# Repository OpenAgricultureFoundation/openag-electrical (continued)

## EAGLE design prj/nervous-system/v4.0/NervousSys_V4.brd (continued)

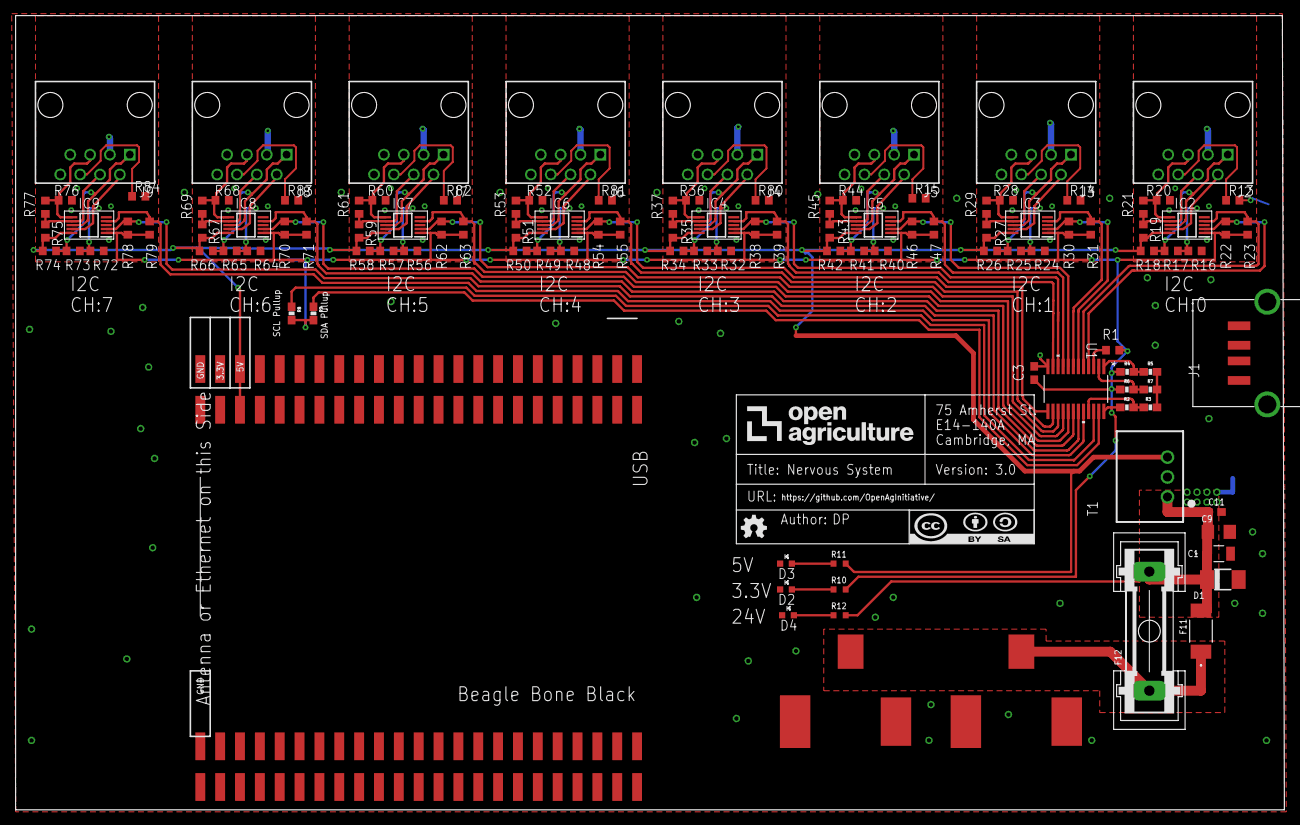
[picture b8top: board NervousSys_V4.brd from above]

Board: 2 copper layers, 162.3 x 101.6 mm, 117 parts (0 on the bottom side), 70 nets.

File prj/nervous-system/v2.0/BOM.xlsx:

Part | Value | Device | Package | Description | Column1 | Column2 | Column3 | Column4 | Column5 | Column6 | Column7 | Column8 | Column9 | Column10 | Column11 | Column12 | Column13 | Column14 | Column15 | Column16 | Column17 | Column18 | Column19 | Column20 | Column21 | Column22 | Column23 | Column24 | Column25
F12 |  | GSH15 | GSH15 | Fuse Holder
C3 | .1uF | C-USC0603 | C0603@1 | 50V or greater
C11 | .1uF | C-USC0603 | C0603@1 | 50V or greater
R1 | 10K | R-US_R0603 | R0603 | 5% tolerance or greater, 1/10W, 0603
R2 | 10K | R-US_R0603 | 0603-RES | 5% tolerance or greater, 1/10W, 0603
R4 | 10K | R-US_R0603 | 0603-RES | 5% tolerance or greater, 1/10W, 0603
R6 | 10K | R-US_R0603 | 0603-RES | 5% tolerance or greater, 1/10W, 0603
R8 | 10K | R-US_R0603 | 0603-RES | 5% tolerance or greater, 1/10W, 0603
R9 | 10K | R-US_R0603 | 0603-RES | 5% tolerance or greater, 1/10W, 0603
R22 | 10K | R-US_R0603 | R0603 | 5% tolerance or greater, 1/10W, 0603
R23 | 10K | R-US_R0603 | R0603 | 5% tolerance or greater, 1/10W, 0604
R30 | 10K | R-US_R0603 | R0603 | 5% tolerance or greater, 1/10W, 0605
R31 | 10K | R-US_R0603 | R0603 | 5% tolerance or greater, 1/10W, 0606
R38 | 10K | R-US_R0603 | R0603 | 5% tolerance or greater, 1/10W, 0607
R39 | 10K | R-US_R0603 | R0603 | 5% tolerance or greater, 1/10W, 0608
R46 | 10K | R-US_R0603 | R0603 | 5% tolerance or greater, 1/10W, 0609
R47 | 10K | R-US_R0603 | R0603 | 5% tolerance or greater, 1/10W, 0610
R54 | 10K | R-US_R0603 | R0603 | 5% tolerance or greater, 1/10W, 0611
R55 | 10K | R-US_R0603 | R0603 | 5% tolerance or greater, 1/10W, 0612
R62 | 10K | R-US_R0603 | R0603 | 5% tolerance or greater, 1/10W, 0613
R63 | 10K | R-US_R0603 | R0603 | 5% tolerance or greater, 1/10W, 0614
R70 | 10K | R-US_R0603 | R0603 | 5% tolerance or greater, 1/10W, 0615
R71 | 10K | R-US_R0603 | R0603 | 5% tolerance or greater, 1/10W, 0616
R78 | 10K | R-US_R0603 | R0603 | 5% tolerance or greater, 1/10W, 0617
R79 | 10K | R-US_R0603 | R0603 | 5% tolerance or greater, 1/10W, 0618
C9 | 10uF | C_US_1206 | C1206 | 50V or greater
R17 | 120 | R-US_R0603 | R0603 | 5% tolerance or greater, 1/10W, 0603
R21 | 120 | R-US_R0603 | R0603 | 5% tolerance or greater, 1/10W, 0604
R25 | 120 | R-US_R0603 | R0603 | 5% tolerance or greater, 1/10W, 0605
R29 | 120 | R-US_R0603 | R0603 | 5% tolerance or greater, 1/10W, 0606
R33 | 120 | R-US_R0603 | R0603 | 5% tolerance or greater, 1/10W, 0607
R37 | 120 | R-US_R0603 | R0603 | 5% tolerance or greater, 1/10W, 0608
R41 | 120 | R-US_R0603 | R0603 | 5% tolerance or greater, 1/10W, 0609
R45 | 120 | R-US_R0603 | R0603 | 5% tolerance or greater, 1/10W, 0610
R49 | 120 | R-US_R0603 | R0603 | 5% tolerance or greater, 1/10W, 0611
R53 | 120 | R-US_R0603 | R0603 | 5% tolerance or greater, 1/10W, 0612
R57 | 120 | R-US_R0603 | R0603 | 5% tolerance or greater, 1/10W, 0613
R61 | 120 | R-US_R0603 | R0603 | 5% tolerance or greater, 1/10W, 0614
R65 | 120 | R-US_R0603 | R0603 | 5% tolerance or greater, 1/10W, 0615
R69 | 120 | R-US_R0603 | R0603 | 5% tolerance or greater, 1/10W, 0616
R73 | 120 | R-US_R0603 | R0603 | 5% tolerance or greater, 1/10W, 0617
R77 | 120 | R-US_R0603 | R0603 | 5% tolerance or greater, 1/10W, 0618
R10 | 200 | R-US_R0603 | RC0603N | 5% tolerance or greater, .25W, 0603
R12 | 4.3K | R-US_R0603 | RC0603N | 5% tolerance or greater, .25W, 0603
J2 | 54602-908LF | OPENAG-V1-RJ45PTH | OPENAG-V1-RJ45 | RJ45 Connector
J3 | 54602-908LF | OPENAG-V1-RJ45PTH | OPENAG-V1-RJ45 | RJ45 Connector
J4 | 54602-908LF | OPENAG-V1-RJ45PTH | OPENAG-V1-RJ45 | RJ45 Connector
J5 | 54602-908LF | OPENAG-V1-RJ45PTH | OPENAG-V1-RJ45 | RJ45 Connector
J6 | 54602-908LF | OPENAG-V1-RJ45PTH | OPENAG-V1-RJ45 | RJ45 Connector
J7 | 54602-908LF | OPENAG-V1-RJ45PTH | OPENAG-V1-RJ45 | RJ45 Connector
J8 | 54602-908LF | OPENAG-V1-RJ45PTH | OPENAG-V1-RJ45 | RJ45 Connector
J9 | 54602-908LF | OPENAG-V1-RJ45PTH | OPENAG-V1-RJ45 | RJ45 Connector
R11 | 560 | R-US_R0603 | RC0603N | 5% tolerance or greater, .25W, 0603
R16 | 600 | R-US_R0603 | R0603 | 5% tolerance or greater, 1/10W, 0603
R18 | 600 | R-US_R0603 | R0603 | 5% tolerance or greater, 1/10W, 0604
R19 | 600 | R-US_R0603 | R0603 | 5% tolerance or greater, 1/10W, 0605
R20 | 600 | R-US_R0603 | R0603 | 5% tolerance or greater, 1/10W, 0606
R24 | 600 | R-US_R0603 | R0603 | 5% tolerance or greater, 1/10W, 0607
R26 | 600 | R-US_R0603 | R0603 | 5% tolerance or greater, 1/10W, 0608
R27 | 600 | R-US_R0603 | R0603 | 5% tolerance or greater, 1/10W, 0609
R28 | 600 | R-US_R0603 | R0603 | 5% tolerance or greater, 1/10W, 0610
R32 | 600 | R-US_R0603 | R0603 | 5% tolerance or greater, 1/10W, 0611
R34 | 600 | R-US_R0603 | R0603 | 5% tolerance or greater, 1/10W, 0612
R35 | 600 | R-US_R0603 | R0603 | 5% tolerance or greater, 1/10W, 0613
R36 | 600 | R-US_R0603 | R0603 | 5% tolerance or greater, 1/10W, 0614
R40 | 600 | R-US_R0603 | R0603 | 5% tolerance or greater, 1/10W, 0615
R42 | 600 | R-US_R0603 | R0603 | 5% tolerance or greater, 1/10W, 0616
R43 | 600 | R-US_R0603 | R0603 | 5% tolerance or greater, 1/10W, 0617
R44 | 600 | R-US_R0603 | R0603 | 5% tolerance or greater, 1/10W, 0618
R48 | 600 | R-US_R0603 | R0603 | 5% tolerance or greater, 1/10W, 0619
R50 | 600 | R-US_R0603 | R0603 | 5% tolerance or greater, 1/10W, 0620
R51 | 600 | R-US_R0603 | R0603 | 5% tolerance or greater, 1/10W, 0621
R52 | 600 | R-US_R0603 | R0603 | 5% tolerance or greater, 1/10W, 0622
R56 | 600 | R-US_R0603 | R0603 | 5% tolerance or greater, 1/10W, 0623
R58 | 600 | R-US_R0603 | R0603 | 5% tolerance or greater, 1/10W, 0624
R59 | 600 | R-US_R0603 | R0603 | 5% tolerance or greater, 1/10W, 0625
R60 | 600 | R-US_R0603 | R0603 | 5% tolerance or greater, 1/10W, 0626
R64 | 600 | R-US_R0603 | R0603 | 5% tolerance or greater, 1/10W, 0627
R66 | 600 | R-US_R0603 | R0603 | 5% tolerance or greater, 1/10W, 0628
R67 | 600 | R-US_R0603 | R0603 | 5% tolerance or greater, 1/10W, 0629
R68 | 600 | R-US_R0603 | R0603 | 5% tolerance or greater, 1/10W, 0630
R72 | 600 | R-US_R0603 | R0603 | 5% tolerance or greater, 1/10W, 0631
R74 | 600 | R-US_R0603 | R0603 | 5% tolerance or greater, 1/10W, 0632
R75 | 600 | R-US_R0603 | R0603 | 5% tolerance or greater, 1/10W, 0633
R76 | 600 | R-US_R0603 | R0603 | 5% tolerance or greater, 1/10W, 0634
J1 | 87583-2010BLF | 87583-2010BLF | CONN_USB-87583 | USB Connector
D2 | APT1608CGCK | APT1608CGCK | CHIPLED_0603 | Indicator LED Green
D3 | APT1608CGCK | APT1608CGCK | CHIPLED_0603 | Indicator LED Green
D4 | APT1608CGCK | APT1608CGCK | CHIPLED_0603 | Indicator LED Green
IC2 | PCA9615DP | PCA9615DP | SOP50P490X110-10N | Buffer IC
IC3 | PCA9615DP | PCA9615DP | SOP50P490X110-10N | Buffer IC
IC4 | PCA9615DP | PCA9615DP | SOP50P490X110-10N | Buffer IC
IC5 | PCA9615DP | PCA9615DP | SOP50P490X110-10N | Buffer IC
IC6 | PCA9615DP | PCA9615DP | SOP50P490X110-10N | Buffer IC
IC7 | PCA9615DP | PCA9615DP | SOP50P490X110-10N | Buffer IC
IC8 | PCA9615DP | PCA9615DP | SOP50P490X110-10N | Buffer IC
IC9 | PCA9615DP | PCA9615DP | SOP50P490X110-10N | Buffer IC
U$1 | PJ-036AH | PJ-036AH | PJ-036AH | 2.1mm Barrel Connector
U$3 | PJ-036AH | PJ-036AH | PJ-036AH | 2.1mm Barrel Connector
T1 | R-78E5.0-1.0 | R-78E5.0-1.0 | R-78E5.0-1.0 | 5V Regulator
U1 | TCA9548APWRPW24-M | TCA9548APWRPW24-M | PW24-M | I2C Mux
Pins | 1528-2021-ND | Pin Header | Pin Header | 2 NEEDED 2:23 .1" spacing can be equivalent component

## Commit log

2017-11-28 initial, partial upload
2017-12-05 pulled in files from distributed repos
2017-12-05 moved scheme to cleaner naming
2017-12-05 initial design changes for light controller v1.1
2017-12-15 pushing to avoid any loss of work
2017-12-16 explored new modularity concept for light controller
2017-12-19 majority of design changes done for light controller v1.1
2017-12-20 sent light controller v1.1 to fab house
2017-12-20 exploring air valves + fans for edu brain
2018-01-03 finalized air valve test pcb
2018-01-09 added custom config scripts
2018-01-09 minor changes to air valve test
2018-01-22 create v1.2 of light controller
2018-01-25 added camera sensor initial design block diagrams
2018-01-30 added new pinout for rj45 w/dI2C + USB
2018-02-02 minor silkscreen changes to light controller v1.2
2018-02-02 Nervous System V2.0
    Nervous System V2.0
2018-02-02 NS V2 Layout Change
2018-02-02 added hotkey config and 5v switching regulator
2018-02-02 NSV2 Changes
2018-02-02 Added Module Folder and RJ45 Buffer
2018-02-02 NSV2
2018-02-02 Added USB to Lib
2018-02-02 NSV2.0 Brd Update
    Photon header, indicator leds etc
2018-02-02 added 24v 1A linear regulator
2018-02-02 cleaned up values and added 1.8V and 3.3V output options
2018-02-04 cleaned up design blocks, added co2 sensor node v2.0
2018-02-05 cleaned up design blocks
2018-02-05 added air sensor node v1.0
2018-02-05 added light sensor node v1.0
2018-02-05 added rj12 adapter
2018-02-05 extracted design blocks from light controller
2018-02-06 NVS Update
2018-02-06 PFC_EDU Structure
2018-02-06 PFC_EDU MECH
2018-02-06 minor changes to air sensor node after design review
2018-02-06 PFC_EDU Models
2018-02-07 pfc edu mechanical
2018-02-07 added light and rj12 nodes, started working on light controller v2
2018-02-07 PFC_EDU
2018-02-07 PFCEDU SCH AND BRD
2018-02-07 PFC EDU LED ARRAY
2018-02-08 added light controller v2.0
2018-02-08 PFC EDU PCB
2018-02-12 added thermal grid sensor
2018-02-12 PFC EDU
2018-02-12 added photon rj45 shield
2018-02-12 fixed via spacing on light controller v2.0
2018-02-12 uploaded gerber files for light controller v2.0
2018-02-12 swapped inductor on light panel v2.0
2018-02-13 added atlas sensor port design block
2018-02-13 added atlas port double v1.0
2018-02-14 added atlas sensor port quad v1.0
2018-02-14 PFC EDU BOM
2018-02-14 pfc-edu renaming
2018-02-14 fied air sensor node solder mask issues
2018-02-14 added easy bom generator
2018-02-15 added manufacturing files for atlas port double v1.0
2018-02-15 updated atlas port quad v1.0 manufacturing files
2018-02-16 added rj12 adapter v1.1
2018-02-16 cleaned up regulator design blocks
2018-02-17 improving keyboard shortcuts
2018-02-18 cleaned up routing on di2c rj45 module
2018-02-19 solidifying style and naming conventions
2018-02-20 experimenting with back cambridge map artwork
2018-02-20 finalized rj12 adapter v1.1
2018-02-20 fixed name issue on rj12 adapter v1.1
2018-02-20 fixed missing csv for rj12 adapter
2018-02-20 progress on light controller v2.1
2018-02-21 light controller v2.1 90% done
2018-02-23 added light controller v2.1
2018-02-23 added photon quad v1.0 at 90%
2018-02-23 added atlas port quad v1.0 and air sensor node v1.1
2018-02-27 pfcedu
2018-03-03 cleaned up design blocks, added light sensor node
2018-03-05 added light controller v2.2
2018-03-05 added BOM for light controlled v2.2
2018-03-05 updated bom for light controller v2.2
2018-03-06 added auto map generation script and applied to light controlled v2.2
2018-03-06 improved readme for map generator
2018-03-06 added process explanation for map generator function
2018-03-08 minor changes
2018-03-08 working on consistent file naming conventions
2018-03-08 added photon rj45 board v2.0
2018-03-08 cleaned up led driver design block for pfc edu
2018-03-15 updated keyboard shortcuts and fixed i2c resistor values on light controller v2.2
2018-03-16 started usb-hub v1.0
2018-03-30 AL8861 LED Driver IC
    New LED Driver IC in Lib
2018-04-03 LED Drver
2018-04-25 mech
2018-06-11 PFC EDU and NVS Changes
2018-06-11 NVS
    NVS
2018-06-27 Lightcontroller3.0
    LC3.0
2018-06-29 6/29/18 Updates
2018-08-21 PCB update
2018-09-05 test
    terst
2018-09-07 PFC EDU
    Airwire, LED+ connection ch1
2018-10-15 PFCEDUandLightController
    PFCEDU
2018-10-15 spec
2018-10-15 Update PFC EDU
2018-10-18 specsheet
2018-10-22 adding readme file for pfc
2018-10-22 removing spec sheet from pfc page
2018-10-22 edited electrical readme pfc
2018-10-22 changed electrical bom name and edited readme
2018-10-22 removed setup from readme in electrical
2018-10-22 reformatted electrical readme
2018-10-22 reformatted readme
    reformatted readme
2018-12-05 added rpi-adapter
    raspberry pi adapter plate to plug into bbb mounting location on PFC
2018-12-19 Added readme to RPI adapter
    RPI to BBB socket adapter, v1.0 has incorrect wiring
2019-01-07 Added boards
    waterbot board, relay board
2019-01-10 Added RJ45 adapter and more
    Added boards
2019-01-17 Added boards (Relay, Display, GPIO, etc)
2019-02-20 added fermentaboard, etc
